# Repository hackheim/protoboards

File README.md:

# Hackheim prototype boards

* [94 x 66mm prototype board](https://github.com/hackheim/protoboards/tree/main/94x66mm)
* Add your amazing board in a subfolder and link it here :)

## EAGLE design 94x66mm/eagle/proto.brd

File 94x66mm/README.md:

# 94 x 66 mm Prototype board

1mm trace width. M3 mounting holes.

Hole spacing: 88.9 x 60.96 - Board size: 93.98 x 66.04.

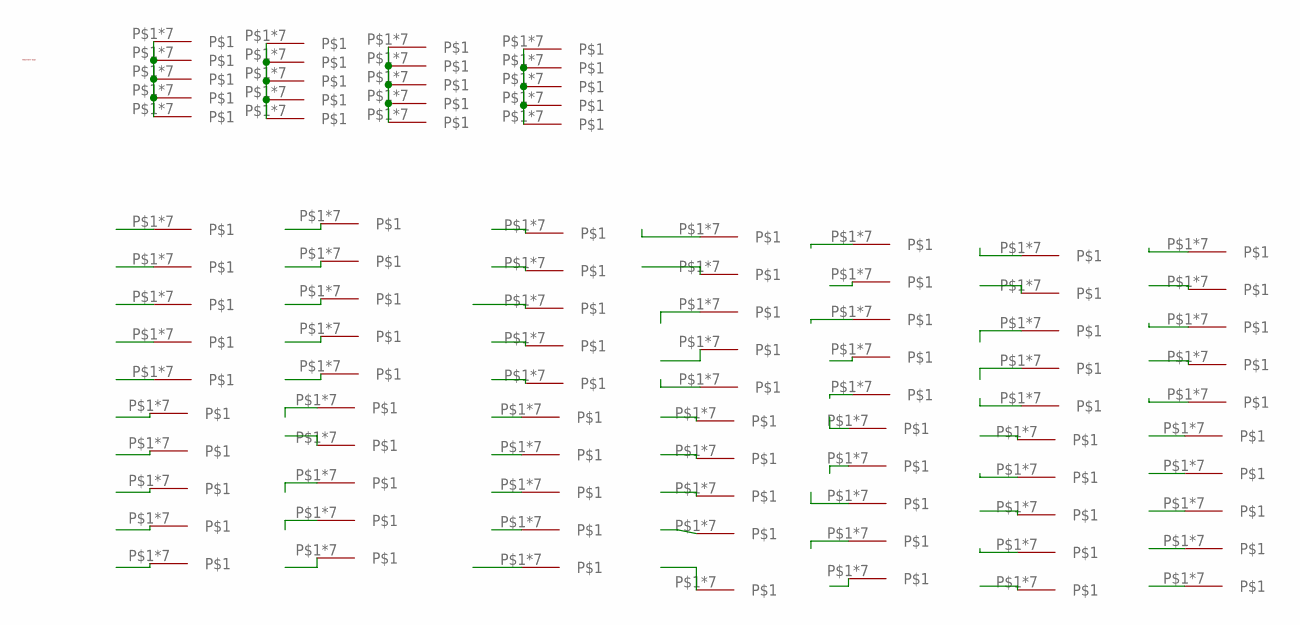
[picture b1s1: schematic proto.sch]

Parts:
U$1: LOGO_HACKHEIM
U$4, U$5, U$6, U$7, U$8, U$9, U$10, U$11, U$12, U$13, U$14, U$15, U$16, U$17, U$18, U$19, U$20, U$21, U$22, U$23, U$24, U$25, U$26, U$27, U$28, U$29, U$30, U$31, U$32, U$33, U$34, U$35, U$36, U$37, U$38, U$39, U$40, U$41, U$42, U$43, U$44, U$45, U$46, U$47, U$48, U$49, U$50, U$51, U$52, U$53, U$54, U$55, U$56, U$57, U$58, U$59, U$60, U$61, U$62, U$63, U$64, U$65, U$66, U$67, U$68, U$69, U$70, U$71, U$72, U$73, U$74, U$75, U$76, U$77, U$78, U$79, U$80, U$81, U$82, U$83, U$84, U$85, U$86, U$87, U$88, U$89, U$90, U$91, U$92, U$93: PROTO_PAD

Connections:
unnamed: U$4.P$1, U$4.P$2, U$4.P$3, U$4.P$4, U$4.P$5, U$4.P$6, U$4.P$7, U$5.P$1, U$5.P$2, U$5.P$3, U$5.P$4, U$5.P$5, U$5.P$6, U$5.P$7, U$6.P$1, U$6.P$2, U$6.P$3, U$6.P$4, U$6.P$5, U$6.P$6, U$6.P$7, U$7.P$1, U$7.P$2, U$7.P$3, U$7.P$4, U$7.P$5, U$7.P$6, U$7.P$7, U$8.P$1, U$8.P$2, U$8.P$3, U$8.P$4, U$8.P$5, U$8.P$6, U$8.P$7
unnamed: U$9.P$1, U$9.P$2, U$9.P$3, U$9.P$4, U$9.P$5, U$9.P$6, U$9.P$7, U$10.P$1, U$10.P$2, U$10.P$3, U$10.P$4, U$10.P$5, U$10.P$6, U$10.P$7, U$11.P$1, U$11.P$2, U$11.P$3, U$11.P$4, U$11.P$5, U$11.P$6, U$11.P$7, U$12.P$1, U$12.P$2, U$12.P$3, U$12.P$4, U$12.P$5, U$12.P$6, U$12.P$7, U$13.P$1, U$13.P$2, U$13.P$3, U$13.P$4, U$13.P$5, U$13.P$6, U$13.P$7
unnamed: U$14.P$1, U$14.P$2, U$14.P$3, U$14.P$4, U$14.P$5, U$14.P$6, U$14.P$7
unnamed: U$15.P$1, U$15.P$2, U$15.P$3, U$15.P$4, U$15.P$5, U$15.P$6, U$15.P$7
unnamed: U$24.P$1, U$24.P$2, U$24.P$3, U$24.P$4, U$24.P$5, U$24.P$6, U$24.P$7, U$25.P$1, U$25.P$2, U$25.P$3, U$25.P$4, U$25.P$5, U$25.P$6, U$25.P$7, U$26.P$1, U$26.P$2, U$26.P$3, U$26.P$4, U$26.P$5, U$26.P$6, U$26.P$7, U$27.P$1, U$27.P$2, U$27.P$3, U$27.P$4, U$27.P$5, U$27.P$6, U$27.P$7, U$28.P$1, U$28.P$2, U$28.P$3, U$28.P$4, U$28.P$5, U$28.P$6, U$28.P$7
unnamed: U$29.P$1, U$29.P$2, U$29.P$3, U$29.P$4, U$29.P$5, U$29.P$6, U$29.P$7, U$30.P$1, U$30.P$2, U$30.P$3, U$30.P$4, U$30.P$5, U$30.P$6, U$30.P$7, U$31.P$1, U$31.P$2, U$31.P$3, U$31.P$4, U$31.P$5, U$31.P$6, U$31.P$7, U$32.P$1, U$32.P$2, U$32.P$3, U$32.P$4, U$32.P$5, U$32.P$6, U$32.P$7, U$33.P$1, U$33.P$2, U$33.P$3, U$33.P$4, U$33.P$5, U$33.P$6, U$33.P$7
unnamed: U$16.P$1, U$16.P$2, U$16.P$3, U$16.P$4, U$16.P$5, U$16.P$6, U$16.P$7
unnamed: U$17.P$1, U$17.P$2, U$17.P$3, U$17.P$4, U$17.P$5, U$17.P$6, U$17.P$7
unnamed: U$18.P$1, U$18.P$2, U$18.P$3, U$18.P$4, U$18.P$5, U$18.P$6, U$18.P$7
unnamed: U$44.P$1, U$44.P$2, U$44.P$3, U$44.P$4, U$44.P$5, U$44.P$6, U$44.P$7
unnamed: U$45.P$1, U$45.P$2, U$45.P$3, U$45.P$4, U$45.P$5, U$45.P$6, U$45.P$7
unnamed: U$46.P$1, U$46.P$2, U$46.P$3, U$46.P$4, U$46.P$5, U$46.P$6, U$46.P$7
unnamed: U$47.P$1, U$47.P$2, U$47.P$3, U$47.P$4, U$47.P$5, U$47.P$6, U$47.P$7
unnamed: U$48.P$1, U$48.P$2, U$48.P$3, U$48.P$4, U$48.P$5, U$48.P$6, U$48.P$7
unnamed: U$19.P$1, U$19.P$2, U$19.P$3, U$19.P$4, U$19.P$5, U$19.P$6, U$19.P$7
unnamed: U$20.P$1, U$20.P$2, U$20.P$3, U$20.P$4, U$20.P$5, U$20.P$6, U$20.P$7
unnamed: U$21.P$1, U$21.P$2, U$21.P$3, U$21.P$4, U$21.P$5, U$21.P$6, U$21.P$7
unnamed: U$22.P$1, U$22.P$2, U$22.P$3, U$22.P$4, U$22.P$5, U$22.P$6, U$22.P$7
unnamed: U$23.P$1, U$23.P$2, U$23.P$3, U$23.P$4, U$23.P$5, U$23.P$6, U$23.P$7
unnamed: U$49.P$1, U$49.P$2, U$49.P$3, U$49.P$4, U$49.P$5, U$49.P$6, U$49.P$7
unnamed: U$50.P$1, U$50.P$2, U$50.P$3, U$50.P$4, U$50.P$5, U$50.P$6, U$50.P$7
unnamed: U$51.P$1, U$51.P$2, U$51.P$3, U$51.P$4, U$51.P$5, U$51.P$6, U$51.P$7
unnamed: U$52.P$1, U$52.P$2, U$52.P$3, U$52.P$4, U$52.P$5, U$52.P$6, U$52.P$7
unnamed: U$34.P$1, U$34.P$2, U$34.P$3, U$34.P$4, U$34.P$5, U$34.P$6, U$34.P$7
unnamed: U$35.P$1, U$35.P$2, U$35.P$3, U$35.P$4, U$35.P$5, U$35.P$6, U$35.P$7
unnamed: U$36.P$1, U$36.P$2, U$36.P$3, U$36.P$4, U$36.P$5, U$36.P$6, U$36.P$7
unnamed: U$37.P$1, U$37.P$2, U$37.P$3, U$37.P$4, U$37.P$5, U$37.P$6, U$37.P$7
unnamed: U$38.P$1, U$38.P$2, U$38.P$3, U$38.P$4, U$38.P$5, U$38.P$6, U$38.P$7
unnamed: U$54.P$1, U$54.P$2, U$54.P$3, U$54.P$4, U$54.P$5, U$54.P$6, U$54.P$7
unnamed: U$55.P$1, U$55.P$2, U$55.P$3, U$55.P$4, U$55.P$5, U$55.P$6, U$55.P$7
unnamed: U$56.P$1, U$56.P$2, U$56.P$3, U$56.P$4, U$56.P$5, U$56.P$6, U$56.P$7
unnamed: U$57.P$1, U$57.P$2, U$57.P$3, U$57.P$4, U$57.P$5, U$57.P$6, U$57.P$7
unnamed: U$58.P$1, U$58.P$2, U$58.P$3, U$58.P$4, U$58.P$5, U$58.P$6, U$58.P$7
unnamed: U$39.P$1, U$39.P$2, U$39.P$3, U$39.P$4, U$39.P$5, U$39.P$6, U$39.P$7
unnamed: U$40.P$1, U$40.P$2, U$40.P$3, U$40.P$4, U$40.P$5, U$40.P$6, U$40.P$7
unnamed: U$41.P$1, U$41.P$2, U$41.P$3, U$41.P$4, U$41.P$5, U$41.P$6, U$41.P$7
unnamed: U$42.P$1, U$42.P$2, U$42.P$3, U$42.P$4, U$42.P$5, U$42.P$6, U$42.P$7
unnamed: U$43.P$1, U$43.P$2, U$43.P$3, U$43.P$4, U$43.P$5, U$43.P$6, U$43.P$7
unnamed: U$59.P$1, U$59.P$2, U$59.P$3, U$59.P$4, U$59.P$5, U$59.P$6, U$59.P$7
unnamed: U$60.P$1, U$60.P$2, U$60.P$3, U$60.P$4, U$60.P$5, U$60.P$6, U$60.P$7
unnamed: U$61.P$1, U$61.P$2, U$61.P$3, U$61.P$4, U$61.P$5, U$61.P$6, U$61.P$7
unnamed: U$62.P$1, U$62.P$2, U$62.P$3, U$62.P$4, U$62.P$5, U$62.P$6, U$62.P$7
unnamed: U$63.P$1, U$63.P$2, U$63.P$3, U$63.P$4, U$63.P$5, U$63.P$6, U$63.P$7
unnamed: U$64.P$1, U$64.P$2, U$64.P$3, U$64.P$4, U$64.P$5, U$64.P$6, U$64.P$7
unnamed: U$65.P$1, U$65.P$2, U$65.P$3, U$65.P$4, U$65.P$5, U$65.P$6, U$65.P$7
unnamed: U$66.P$1, U$66.P$2, U$66.P$3, U$66.P$4, U$66.P$5, U$66.P$6, U$66.P$7
unnamed: U$67.P$1, U$67.P$2, U$67.P$3, U$67.P$4, U$67.P$5, U$67.P$6, U$67.P$7
unnamed: U$68.P$1, U$68.P$2, U$68.P$3, U$68.P$4, U$68.P$5, U$68.P$6, U$68.P$7
unnamed: U$69.P$1, U$69.P$2, U$69.P$3, U$69.P$4, U$69.P$5, U$69.P$6, U$69.P$7
unnamed: U$70.P$1, U$70.P$2, U$70.P$3, U$70.P$4, U$70.P$5, U$70.P$6, U$70.P$7
unnamed: U$71.P$1, U$71.P$2, U$71.P$3, U$71.P$4, U$71.P$5, U$71.P$6, U$71.P$7
unnamed: U$72.P$1, U$72.P$2, U$72.P$3, U$72.P$4, U$72.P$5, U$72.P$6, U$72.P$7
unnamed: U$73.P$1, U$73.P$2, U$73.P$3, U$73.P$4, U$73.P$5, U$73.P$6, U$73.P$7
unnamed: U$74.P$1, U$74.P$2, U$74.P$3, U$74.P$4, U$74.P$5, U$74.P$6, U$74.P$7
unnamed: U$75.P$1, U$75.P$2, U$75.P$3, U$75.P$4, U$75.P$5, U$75.P$6, U$75.P$7
unnamed: U$76.P$1, U$76.P$2, U$76.P$3, U$76.P$4, U$76.P$5, U$76.P$6, U$76.P$7
unnamed: U$77.P$1, U$77.P$2, U$77.P$3, U$77.P$4, U$77.P$5, U$77.P$6, U$77.P$7
unnamed: U$78.P$1, U$78.P$2, U$78.P$3, U$78.P$4, U$78.P$5, U$78.P$6, U$78.P$7
unnamed: U$79.P$1, U$79.P$2, U$79.P$3, U$79.P$4, U$79.P$5, U$79.P$6, U$79.P$7
unnamed: U$80.P$1, U$80.P$2, U$80.P$3, U$80.P$4, U$80.P$5, U$80.P$6, U$80.P$7
unnamed: U$81.P$1, U$81.P$2, U$81.P$3, U$81.P$4, U$81.P$5, U$81.P$6, U$81.P$7
unnamed: U$82.P$1, U$82.P$2, U$82.P$3, U$82.P$4, U$82.P$5, U$82.P$6, U$82.P$7
unnamed: U$83.P$1, U$83.P$2, U$83.P$3, U$83.P$4, U$83.P$5, U$83.P$6, U$83.P$7
unnamed: U$84.P$1, U$84.P$2, U$84.P$3, U$84.P$4, U$84.P$5, U$84.P$6, U$84.P$7
unnamed: U$85.P$1, U$85.P$2, U$85.P$3, U$85.P$4, U$85.P$5, U$85.P$6, U$85.P$7
unnamed: U$86.P$1, U$86.P$2, U$86.P$3, U$86.P$4, U$86.P$5, U$86.P$6, U$86.P$7
unnamed: U$87.P$1, U$87.P$2, U$87.P$3, U$87.P$4, U$87.P$5, U$87.P$6, U$87.P$7
unnamed: U$88.P$1, U$88.P$2, U$88.P$3, U$88.P$4, U$88.P$5, U$88.P$6, U$88.P$7
unnamed: U$89.P$1, U$89.P$2, U$89.P$3, U$89.P$4, U$89.P$5, U$89.P$6, U$89.P$7
unnamed: U$90.P$1, U$90.P$2, U$90.P$3, U$90.P$4, U$90.P$5, U$90.P$6, U$90.P$7
unnamed: U$91.P$1, U$91.P$2, U$91.P$3, U$91.P$4, U$91.P$5, U$91.P$6, U$91.P$7
unnamed: U$92.P$1, U$92.P$2, U$92.P$3, U$92.P$4, U$92.P$5, U$92.P$6, U$92.P$7
unnamed: U$93.P$1, U$93.P$2, U$93.P$3, U$93.P$4, U$93.P$5, U$93.P$6, U$93.P$7
unnamed: U$53.P$1, U$53.P$2, U$53.P$3, U$53.P$4, U$53.P$5, U$53.P$6, U$53.P$7

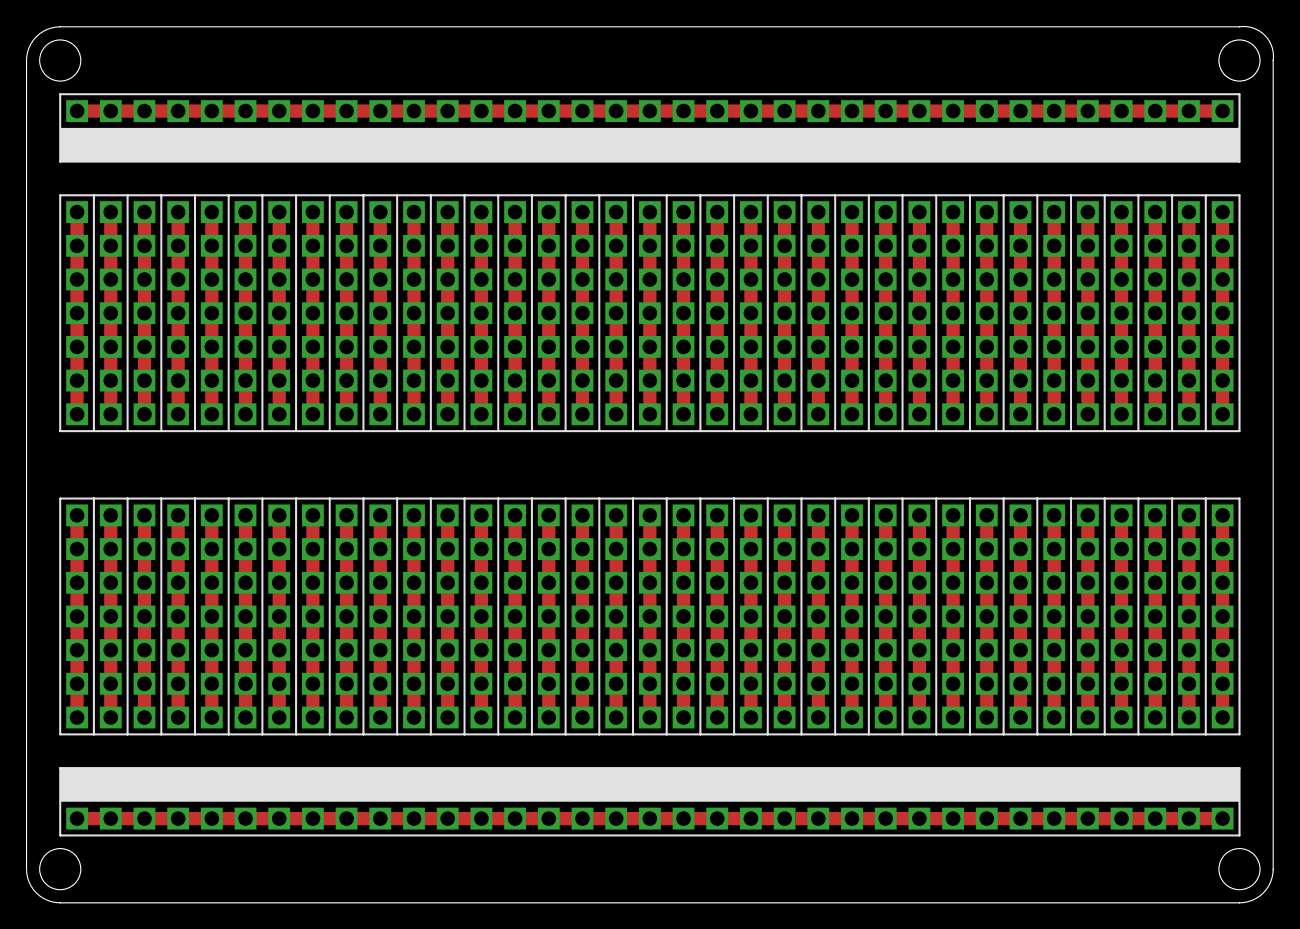
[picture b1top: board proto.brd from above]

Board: 2 copper layers, 94.0 x 66.1 mm, 91 parts (1 on the bottom side), 74 nets.

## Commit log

2023-09-06 Added basic protype brd/sch + gerber files
